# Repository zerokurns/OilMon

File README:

This is a simple eagle schematic and board file to interface a particle proton with a float sensor. The project is not important, it's simply a chance for me to learn git and GitHub a bit.

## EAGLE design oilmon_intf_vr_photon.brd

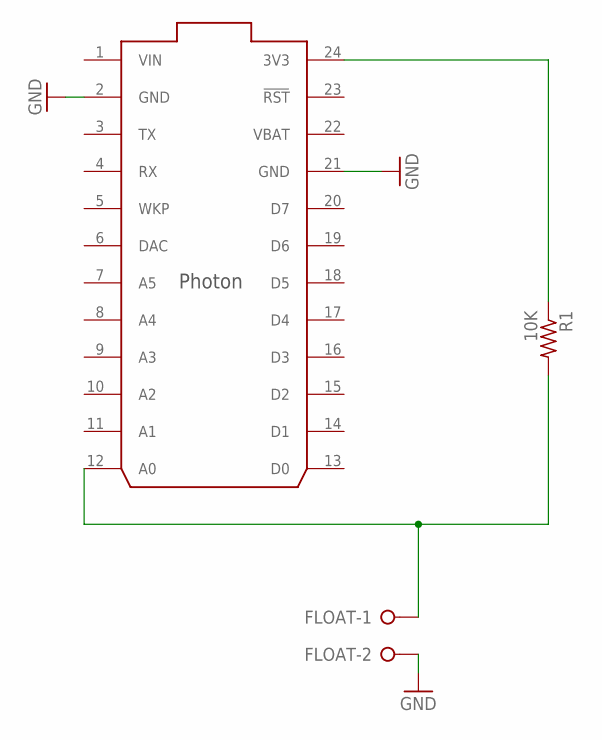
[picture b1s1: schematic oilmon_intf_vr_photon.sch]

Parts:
FLOAT: W237-02P; W237-132
PHOTON: PHOTON_WITH_HEADERS; PHOTON
R1: 10K; 0207/10

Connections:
GND: FLOAT.2, PHOTON.2 (GND), PHOTON.21 (GND)
unnamed: PHOTON.24 (3V3), R1.1
unnamed: FLOAT.1, PHOTON.12 (A0), R1.2
VBAT: PHOTON.22 (VBAT)
VIN: PHOTON.1 (VIN)

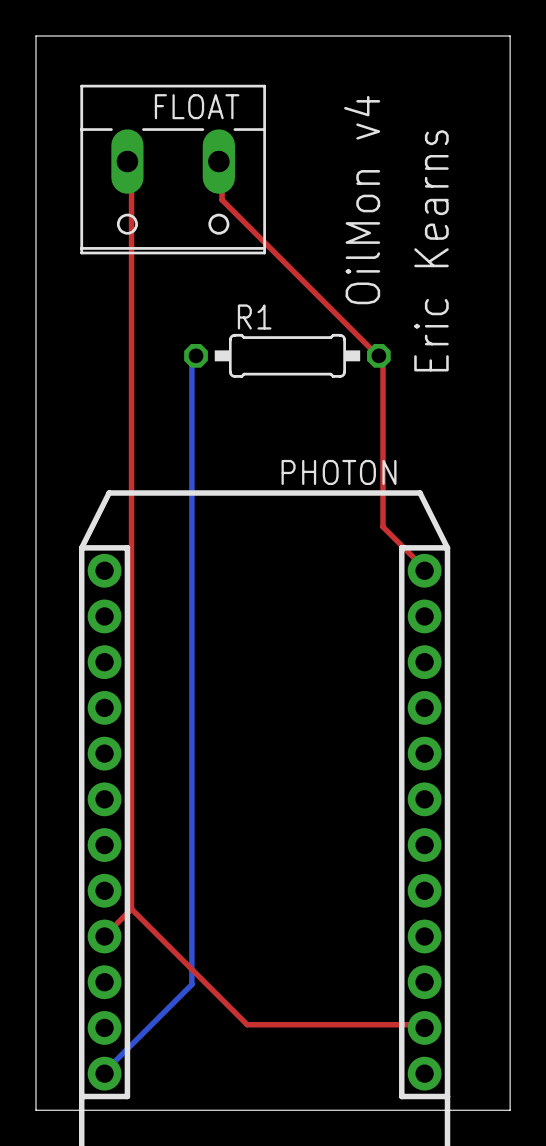
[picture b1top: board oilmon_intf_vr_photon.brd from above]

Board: 2 copper layers, 26.3 x 59.7 mm, 3 parts (0 on the bottom side), 3 nets.

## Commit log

2015-10-20 Add existing eagle project files
2015-10-20 Remove redundant files
2015-10-20 Added README file
